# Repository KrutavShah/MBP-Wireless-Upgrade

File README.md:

# MBP-Wireless-Upgrade

A simple solution that allows you to upgrade your Unibody MacBook Pro wireless card to meet today's standards.

## So what is it?
This GitHub page contains schematics and models that you can use to buid your very own WiFi card to upgrade an Apple unibody MacBook Pro! (Not ready yet, but is coming soon.)
Macbooks manufactured prior to the 2nd half of 2012 like the 2011 MacBook Pro 15 inch include a WiFi + Bluetooth card that is considered to be lacking in functionality compared to today's standards. WiFi speed on these older cards top out at 450Mbps, which is a lot less than what most wireless routers are capable of today. In addition, the Bluetooth version is 3.0 on all models manufactured prior to 2012, something that may become problematic with newer devices and AirDrop.

## What is the progress so far?
Tthe Universal Adapter for all MacBooks is available for download and fabrication by downloadin the zip fle in the releases section. Upload it to JLCPCB and select the options that suit you best, such as your desired PCB thickness, PCB color, and specify the order number location so that it is printed where it's not visible. 

## So why should you upgrade your MacBook if it is a decade old?
Well if you're like me and don't want to shell out a lot of money for one of Apple's new offerings, this upgrade can allow you to hold on to your MacBook for longer. With this upgrade, you get a newer version of Bluetooth 4 which allows you to use AirDrop and connect to most modern devices. You also get a much faster WiFi unit which can allow you to achieve speeds of over 1 Gigabit and take full potential of your home network.
The improvements:
- Access to 802.11 AC WiFi for speeds up to 1.3Gbps
- Up to Bluetooth 4.2 for improved range and speeds, as well as compatibility with more devices
- Newer technology, which means lower power consumption and better efficiency.
  
### Licensing information
This work is licensed under a
[Creative Commons Attribution-NonCommercial-NoDerivatives 4.0 International License][cc-by-nc-nd].

Distribution and modification of this project without giving proper credits is not allowed. For commercial usage of this project, the express permission of the project maintainer is necessary.

[![CC BY-NC-ND 4.0][cc-by-nc-nd-image]][cc-by-nc-nd]

[cc-by-nc-nd]: http://creativecommons.org/licenses/by-nc-nd/4.0/
[cc-by-nc-nd-image]: https://licensebuttons.net/l/by-nc-nd/4.0/88x31.png

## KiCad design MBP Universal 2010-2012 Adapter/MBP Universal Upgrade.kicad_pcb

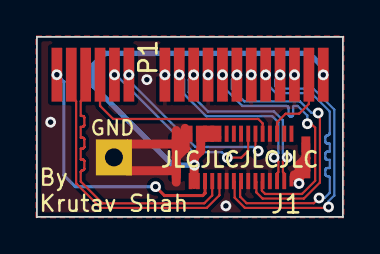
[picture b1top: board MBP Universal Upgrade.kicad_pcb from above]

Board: 2 copper layers, 17.0 x 10.0 mm, 3 parts (0 on the bottom side), 15 nets.

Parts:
J1: Molex 501745-0301; 5017450301
MH1: GND Hole; MountingHole_2.2mm_M2_DIN965_Pad
P1: Edge Connector

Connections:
/AP_PCIE_WAKE_L: J1.12, P1.13
/PCIE_AP_R2D_N: J1.17, P1.4
/PCIE_AP_R2D_P: J1.15, P1.5
/PCIE_CLK100M_AP_N: J1.11, P1.7
/PCIE_CLK100M_AP_P: J1.9, P1.8
AP_CLKREQ_Q_L: J1.10, P1.15
AP_RESET_CONN_L: J1.14, P1.14
GND: J1.1, J1.7, J1.8, J1.13, J1.16, J1.19, J1.30, J1.31, J1.32, J1.33, J1.34, MH1.1, P1.3, P1.6, P1.9, P1.12
PCIE_AP_D2R_N: J1.5, P1.11
PCIE_AP_D2R_P: J1.3, P1.10
PP3V3_S3_BT_F: J1.25, P1.18
PP3V3_WLAN: J1.22, J1.24, J1.26, J1.27, J1.28, J1.29, P1.1
USB_BT_N: J1.23, P1.16
USB_BT_P: J1.21, P1.17
WIFI_EVENT_L: J1.6, P1.2

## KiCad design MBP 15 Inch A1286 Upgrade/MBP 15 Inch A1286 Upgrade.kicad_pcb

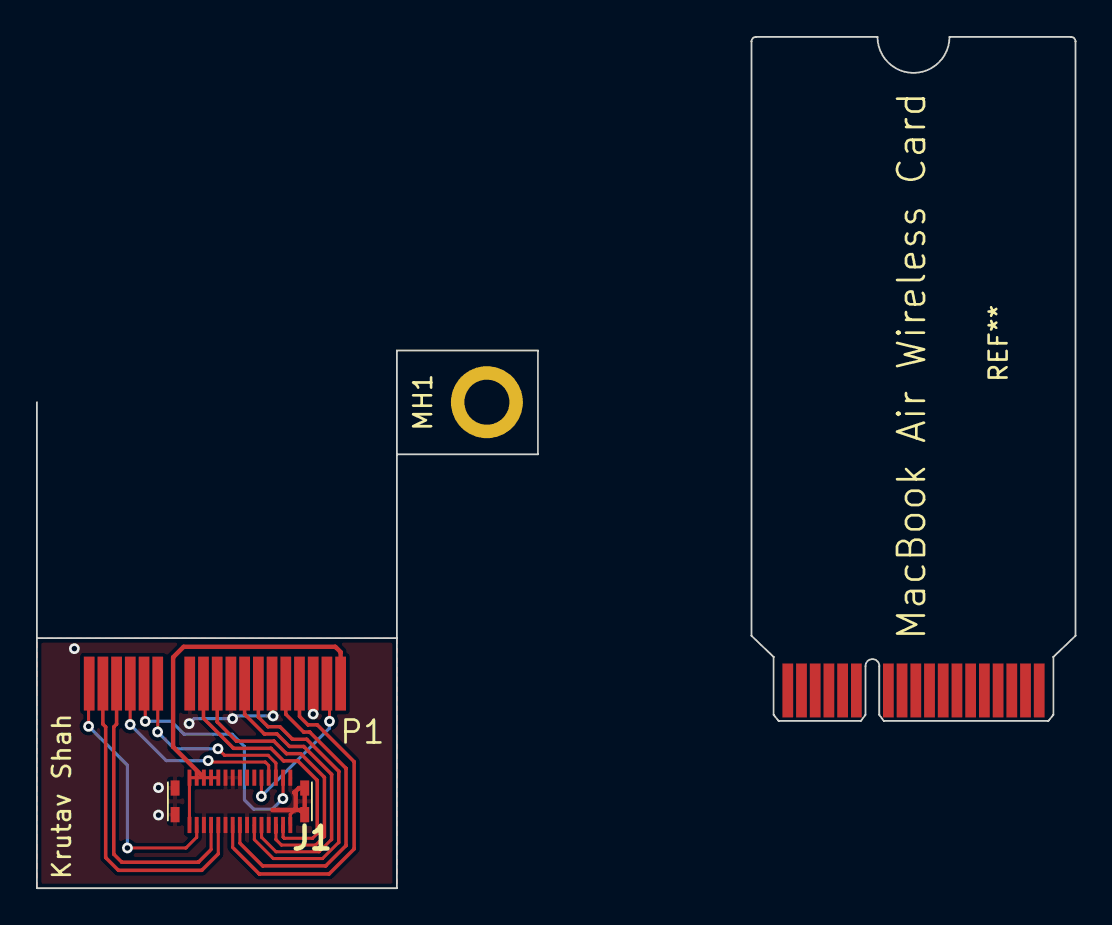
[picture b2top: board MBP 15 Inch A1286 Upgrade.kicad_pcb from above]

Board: 2 copper layers, 57.7 x 47.3 mm, 3 parts (0 on the bottom side), 15 nets.

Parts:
J1: 501745-0301; 5017450301
MH1: MountingHole_2.5mm_Pad
P1: (no value)

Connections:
AP_CLKREQ_Q_L: J1.8, P1.15
AP_PCIE_WAKE_L: J1.6, P1.13
AP_RESET_CONN_L: J1.4, P1.14
GND: J1.1, J1.2, J1.7, J1.13, J1.16, J1.18, J1.19, J1.20, J1.25, J1.31, J1.32, J1.33, J1.34, P1.3, P1.6, P1.9, P1.12
PCIE_AP_D2R_N: J1.5, P1.10
PCIE_AP_D2R_P: J1.3, P1.11
PCIE_AP_R2D_N: J1.17, P1.4
PCIE_AP_R2D_P: J1.15, P1.5
PCIE_CLK100M_AP_N: J1.11, P1.7
PCIE_CLK100M_AP_P: J1.9, P1.8
PP3V3_S3_BT_F: J1.27, P1.18
PP3V3_WLAN: J1.22, J1.24, J1.26, J1.28, J1.29, J1.30, P1.1
USB_BT_N: J1.23, P1.16
USB_BT_P: J1.21, P1.17
WIFI_EVENT_L: J1.10, P1.2

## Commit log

2021-01-31 Adding the Licenses
2021-01-31 Added License
2021-02-17 Initial KiCad files add
2021-02-24 Updated items
2021-02-26 Fixed broken files
2021-02-26 Added Wireless Card Connector
2021-02-27 Added 15-inch 1st revision
2021-02-27 Updated 2009 15-inch adapter
2021-02-27 Changed License
2021-02-27 Fixed model numbers
2021-02-27 Updated Licensing
2021-02-27 Deleted temporary files and added images
2021-02-27 Fixed image name
2021-02-27 Updated board
2021-02-28 Added some measurements
2021-03-02 Renamed Folders
2021-03-06 Updated the adapter
2021-03-08 Release prototype for Universal part ready.
2021-03-09 Added pre-release fabrication files
2021-03-09 Made updates for pre-release
2021-04-04 Made large changes and fixes to the adapter
2021-04-06 Matched trace lengths
2021-06-17 Improved and redesigned in Altium.
2021-06-20 Fixed (critical) incorrect spacing for V2 design.
2021-07-28 Uploaded all updated files. This design is production ready and soon to be on Krutav.com
